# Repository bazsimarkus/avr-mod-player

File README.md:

# avr-mod-player

An ATmega32-based ProTracker MOD music player with AM29F040B parallel flash memory and stereo PWM audio output. Program a MOD file onto the flash chip, plug it in, and music starts playing.

---

## Table of Contents

- [Overview](#overview)
- [Features](#features)
- [Getting Started](#getting-started)
  - [What You Need](#what-you-need)
  - [Programming the Flash Chip](#programming-the-flash-chip)
  - [Building and Flashing the Firmware](#building-and-flashing-the-firmware)
- [Schematic](#schematic)
  - [Bill of Materials for the Main Board](#bill-of-materials-for-the-main-board)
- [How It Works](#how-it-works)
  - [Flash Memory Interface](#flash-memory-interface)
  - [Audio Output](#audio-output)
  - [MOD Playback Engine](#mod-playback-engine)
  - [Channel Activity LEDs](#channel-activity-leds)
  - [Power Supply and Protection](#power-supply-and-protection)
- [Speaker Extension Board](#speaker-extension-board)
  - [Bill of Materials for the Speaker Extension Board](#bill-of-materials-for-the-speaker-extension-board)
- [Documentation](#documentation)
- [Acknowledgments](#acknowledgments)

---

## Overview

This is a standalone hardware MOD file player built around the ATmega32A microcontroller. It reads ProTracker .MOD files directly from an AM29F040B parallel NOR flash chip and outputs stereo audio through RCA connectors using PWM and analog filtering. Four green LEDs flash in time with the music, one per channel, showing which voices are active.

The concept is simple: program a MOD file onto the flash chip, plug it into the socket, flip the power switch, and music starts playing immediately. No SD cards, no file systems, no menus. Just a chip full of music and a microcontroller that knows how to play it. If you want to listen to a different track, pull the flash chip out of its socket, erase it, program a new file, and put it back.

My main inspiration was [MadWizard's AVR MOD player](https://www.madwizard.org/electronics/projects/modplayer). That project also used the AM29F040 flash chip, which led me down this path. Since I had no way to program these chips, I ended up designing my own flash programmer, available as a separate project: [amd-flash-programmer](https://github.com/bazsimarkus/amd-flash-programmer).

---

## Features

- ATmega32A microcontroller running at 16 MHz external crystal
- AM29F040B 512KB parallel NOR flash for MOD file storage (socketed for easy swapping)
- Stereo audio output through dual RCA connectors
- MCP6022 dual rail-to-rail op-amp based analog output filtering
- 74HC595 shift register driving four green 3mm channel activity LEDs
- 4-channel ProTracker MOD format playback with effects (arpeggio, portamento, vibrato, volume slide, and more)
- 16 kHz PWM sample rate via Timer1, stereo hard-panned per ProTracker convention (channels 1 and 4 left, channels 2 and 3 right)
- 10-pin ISP header for in-circuit programming via USBasp
- 9-12V DC barrel jack power input with L7805 5V regulator
- 1N5819 Schottky diode protection preventing backfeed between DC jack and ISP programmer power
- ON/OFF toggle switch and reset button
- Pin header for the optional LM386 speaker extension board
- Designed in KiCad, full schematic and PCB files included

---

## Getting Started

### What You Need

- The assembled AVR MOD Player board
- A USBasp programmer (or any AVR ISP programmer)
- A way to program the AM29F040B flash chip (e.g. [amd-flash-programmer](https://github.com/bazsimarkus/amd-flash-programmer))
- A ProTracker .MOD file (max 512KB to fit on the flash chip)
- avr-gcc and avrdude installed on your system
- An RCA audio cable or the speaker extension board for output

### Programming the Flash Chip

1. Find a MOD file you want to play. [The Mod Archive](https://modarchive.org/) has a large collection of free tracks. Some personal favorites: Maktone - Vanishing Colors, LHS - It's a Good Day, Random Voice - Monday.

2. Remove the AM29F040B from its socket on the player board.

3. Program the raw .MOD file onto the flash chip starting at address 0x00000 using the [amd-flash-programmer](https://github.com/bazsimarkus/amd-flash-programmer) or any compatible flash programmer.

4. Place the programmed flash chip back into the socket on the player board.

5. Flip the power switch. The music starts playing immediately.

### Building and Flashing the Firmware

The firmware is a single C source file (`avr-mod-player/main.c`) targeting the ATmega32A at 16 MHz. It has no external dependencies beyond standard avr-libc. It links against libm for the math routines.

#### Method 1: Command line with avr-gcc and avrdude

Install avr-gcc and avrdude for your platform (on Debian/Ubuntu: `sudo apt install gcc-avr avr-libc avrdude`; on Windows, install WinAVR or the Microchip AVR toolchain).

Navigate to the `avr-mod-player` directory and run:

```sh
avr-gcc -mmcu=atmega32 -DF_CPU=16000000UL -O1 \
    -funsigned-char -funsigned-bitfields \
    -ffunction-sections -fdata-sections \
    -fpack-struct -fshort-enums \
    -Wall -o main.elf main.c -lm

avr-objcopy -O ihex main.elf main.hex
```

Then flash with your USBasp programmer:

```sh
avrdude -c usbasp -p m32 -U flash:w:main.hex
```

#### Method 2: MPLAB X IDE

The repository includes an MPLAB X IDE project in the `avr-mod-player/nbproject` directory. The project has two build configurations:

- **default**: Compiles only, produces the hex file.
- **flash**: Identical to default, but runs avrdude automatically after a successful build to flash the connected board via USBasp. The post-build step is:

```
avrdude -c usbasp -p m32 -U flash:w:${ImagePath}
```

With the flash configuration selected, clicking Build Main Project compiles the firmware and programs the board in a single step.

The project was developed with MPLAB X IDE v6.25 and the Microchip ATmega_DFP 3.3.279 device pack. The compiler is avr-gcc 5.4.0.

---

## Schematic

The full KiCad project files (schematic, PCB layout, and project file) are in the `schematic/` directory.

### Bill of Materials for the Main Board

| Ref | Value | Description | Qty |
|-----|-------|-------------|-----|
| **ICs** ||||
| U1 | ATmega32A-P | 16 MHz, 32 KB Flash, 2 KB SRAM, DIP-40 | 1 |
| U2 | AM29F040B-90PC | 4 Mbit NOR flash (512K×8), 90 ns, DIP-32 | 1 |
| U3 | 74HC595 | 8-bit shift register, 3-state outputs, DIP-16 | 1 |
| U4 | MCP6022 | Dual rail-to-rail op-amp, DIP-8 | 1 |
| U5 | L7805 | 5 V 1.5 A linear voltage regulator, TO-220 | 1 |
| **Crystal** ||||
| Y1 | 16 MHz | HC49-U vertical | 1 |
| **Capacitors (polarized)** ||||
| C1 | 10 µF | Electrolytic, radial, D4.0 mm P2.00 mm | 1 |
| C7 | 220 µF | Electrolytic, radial, D5.0 mm P2.00 mm | 1 |
| C8 | 220 µF | Electrolytic, radial, D5.0 mm P2.00 mm | 1 |
| C9 | 10 µF | Electrolytic, radial, D4.0 mm P2.00 mm | 1 |
| C12 | 10 µF | Electrolytic, radial, D4.0 mm P2.00 mm | 1 |
| **Capacitors (unpolarized)** ||||
| C2 | 100 nF | Film/MLCC, P5.00 mm | 1 |
| C3 | 22 pF | Ceramic, P2.50 mm | 1 |
| C4 | 22 pF | Ceramic, P2.50 mm | 1 |
| C5 | 10 nF | Ceramic disc, P2.50 mm | 1 |
| C6 | 10 nF | Ceramic disc, P2.50 mm | 1 |
| C10 | 0.33 µF | Film, P5.00 mm | 1 |
| C11 | 0.1 µF | Film, P5.00 mm | 1 |
| C13 | 100 nF | Film/MLCC, P5.00 mm | 1 |
| C14 | 100 nF | Film/MLCC, P5.00 mm | 1 |
| C15 | 100 nF | Film/MLCC, P5.00 mm | 1 |
| **Resistors (all 1/4 W axial)** ||||
| R1, R2 | 4.7 kΩ | PWM filter pull-up | 2 |
| R3, R4, R7, R8, R9, R10, R12 | 10 kΩ | Pull-ups / biasing / LED current limit | 7 |
| R5, R6 | 1 kΩ | Audio output series | 2 |
| R11 | 470 Ω | Power LED current limiter | 1 |
| **Diodes** ||||
| D1, D2, D3, D4 | LED 3 mm green | Channel activity indicators | 4 |
| D5 | 1N4001 | 50 V 1 A rectifier, DO-41 | 1 |
| D6 | LED 5 mm red | Power indicator | 1 |
| D7 | 1N5819 | 40 V 1 A Schottky, DO-41 (reverse polarity protection) | 1 |
| **Switches** ||||
| S1 | Toggle 7×7 mm DPDT | Power on/off (E-Switch TL2230OAF140) | 1 |
| S2 | Tact 6×6 mm | Reset (CUI TS02-66-100-BK-260-LCR-D) | 1 |
| **Connectors** ||||
| J1 | 2×5 shrouded box header | USBasp ISP header (Würth 61201021621) | 1 |
| J2 | DC-005 barrel jack | 2.1 mm center-positive | 1 |
| J3 | Dual RCA (AV2-8.4-45) | Stereo audio output | 1 |
| J4 | 2×4 pin socket | Speaker board expansion, 2.54 mm | 1 |
| **Recommended sockets** ||||
| - | 40-pin DIP socket | For U1 (ATmega32A) | 1 |
| - | 32-pin DIP socket | For U2 (AM29F040B) | 1 |
| - | 16-pin DIP socket | For U3 (74HC595) | 1 |
| - | 8-pin DIP socket | For U4 (MCP6022) | 1 |

---

## How It Works

### Flash Memory Interface

The AM29F040B is a 512KB parallel NOR flash chip in a 32-pin DIP package. The ATmega32A addresses it using nearly all of its available I/O pins:

- PORTA (PA0-PA7): Address lines A0-A7
- PORTB (PB0-PB7): Address lines A8-A15
- PORTD (PD0-PD2): Address lines A16-A18
- PORTC (PC0-PC7): Data bus DQ0-DQ7 (configured as input)

This gives 19 address lines, enough for the full 512KB address space. The chip enable (CE#) and output enable (OE#) pins are active (directly connected to ground), meaning the flash is always outputting data on the bus. The write enable (WE#) pin is pulled high permanently with a resistor, since the player board never writes to the flash. This simplified design was necessary because the ATmega32A does not have enough free pins to control WE# dynamically.

Reading a byte from flash is a single function call: set PORTA, PORTB, and the lower bits of PORTD to the desired address, wait two CPU cycles for the flash access time, then read PINC. At 16 MHz, this gives about 187 ns of access time, well within the 90 ns rating of the AM29F040B-90PC.

### Audio Output

Stereo audio is generated using Timer1 in 8-bit fast PWM mode. The two PWM outputs (OC1A on PD5 for left, OC1B on PD4 for right) run at a carrier frequency of 62.5 kHz (16 MHz / 256), which is well above the audible range.

The raw PWM signals pass through a low-pass filter built around the MCP6022 dual rail-to-rail op-amp. Each channel has its own filter section: a 10nF capacitor and a 4.7k resistor form the RC low-pass, and the op-amp buffers and drives the output through a 220uF coupling capacitor to the RCA connector. The coupling capacitor removes the DC offset so only the audio AC signal reaches the amplifier or speakers.

### MOD Playback Engine

The firmware implements a ProTracker-compatible 4-channel MOD player. Timer0 fires an interrupt at exactly 16,000 Hz, which pulls samples from a ring buffer and writes them to the PWM registers. The main loop continuously fills that buffer by mixing the four channels.

The MOD file format stores music as a sequence of patterns. Each pattern has 64 rows, and each row has four cells (one per channel). Each cell can trigger a sample at a given pitch, change the volume, or apply an effect. At startup, the firmware parses the MOD header from flash to locate the sample data and pattern data, then begins sequencing through the song.

The engine supports the following ProTracker effects:

- 0xy: Arpeggio
- 1xx: Portamento up
- 2xx: Portamento down
- 3xx: Tone portamento
- 4xy: Vibrato
- 9xx: Sample offset
- Axy: Volume slide
- Bxx: Pattern jump
- Cxx: Set volume
- Dxx: Pattern break
- Fxx: Set speed/tempo
- E1y/E2y: Fine portamento
- E9y: Retrigger note
- EAy/EBy: Fine volume slide
- ECy: Note cut

Pitch is calculated using 16.16 fixed-point arithmetic. The playback step for each channel is derived from the Amiga PAL clock constant (3,546,895 Hz) divided by the channel's current period value, scaled to the 16 kHz output rate. This gives sample-accurate pitch reproduction matching the original Amiga hardware.

The MOD file format specification used to build this player is included in the repository at `docs/mod-spec.txt` (sourced from [eblong.com/zarf/blorb/mod-spec.txt](https://www.eblong.com/zarf/blorb/mod-spec.txt)).

### Channel Activity LEDs

Four green 3mm LEDs (D1-D4) are driven by a 74HC595 shift register connected to three pins on PORTD. Each time a note triggers on a channel, the corresponding LED lights up for approximately 60 milliseconds (3 sequencer ticks). This creates a short flash locked to the beat, giving a visual indication of which channels are active. The LEDs are updated once per sequencer tick in the main audio loop.

### Power Supply and Protection

The board is powered from a 9-12V DC barrel jack. An L7805 voltage regulator provides the 5V rail for all digital and analog circuitry. A 1N4001 rectifier diode on the DC input provides reverse polarity protection.

A 1N5819 Schottky diode sits between the ISP header's VCC pin and the board's 5V rail. When the board is powered from the DC jack, the Schottky diode prevents the regulated 5V from backfeeding into the programmer. When the board is powered from the programmer (for firmware development without the DC supply connected), the Schottky diode conducts and powers the board from the programmer's VCC. This protects both the L7805 regulator and the programmer from conflicting voltage sources.

---

## Speaker Extension Board

An optional LM386 speaker extension board can be connected to the 2x4 pin header (J4) on the main board. It mixes the left and right channels through two 300k resistors into a volume trimmer, feeds the signal through an LM386 audio power amplifier, and drives a small 23mm 8-ohm speaker. The board connects directly to the pin header and receives both audio signals and power from the main board.

The KiCad project files for the speaker board are in `extension-boards/speaker-board/`.

### Bill of Materials for the Speaker Extension Board

| Ref | Value | Description | Qty |
|-----|-------|-------------|-----|
| **ICs** ||||
| U1 | LM386 | Low-voltage audio power amplifier, DIP-8 | 1 |
| **Capacitors (polarized)** ||||
| C1 | 100 µF | Electrolytic, radial, D5.0 mm P2.00 mm | 1 |
| C3 | 1 µF | Electrolytic, radial, D4.0 mm P2.00 mm | 1 |
| C4 | 10 µF | Electrolytic, radial, D4.0 mm P2.00 mm (bypass) | 1 |
| C6 | 220 µF | Electrolytic, radial, D5.0 mm P2.00 mm (output coupling) | 1 |
| **Capacitors (unpolarized)** ||||
| C2 | 0.1 µF | Film, P5.00 mm (decoupling) | 1 |
| C5 | 47 nF | Ceramic disc, P2.50 mm (Zobel network) | 1 |
| **Resistors (all 1/4 W axial)** ||||
| R1, R2 | 300 kΩ | Input mixing (L + R → mono) | 2 |
| R3 | 10 Ω | Zobel network series | 1 |
| **Potentiometer** ||||
| RV1 | Trimpot 3362-P | Volume adjustment | 1 |
| **Speaker** ||||
| LS1 | CVS-2308 | 23 mm, 0.1 W, 8 Ω (CUI Devices) | 1 |
| **Connectors** ||||
| J1 | 2×4 pin header | Mates with main board J4, 2.54 mm vertical | 1 |
| **Recommended sockets** ||||
| - | 8-pin DIP socket | For U1 (LM386) | 1 |

---

## Documentation

The `docs/` directory contains:

- `mod-spec.txt`: The ProTracker MOD file format specification used as reference for the playback engine (from [eblong.com](https://www.eblong.com/zarf/blorb/mod-spec.txt))

---

## Acknowledgments

- [MadWizard](https://www.madwizard.org/electronics/projects/modplayer) for the original AVR MOD player project that inspired this build
- [The Mod Archive](https://modarchive.org/) for the collection of freely available MOD files
- The ProTracker MOD format specification from [eblong.com](https://www.eblong.com/zarf/blorb/mod-spec.txt)

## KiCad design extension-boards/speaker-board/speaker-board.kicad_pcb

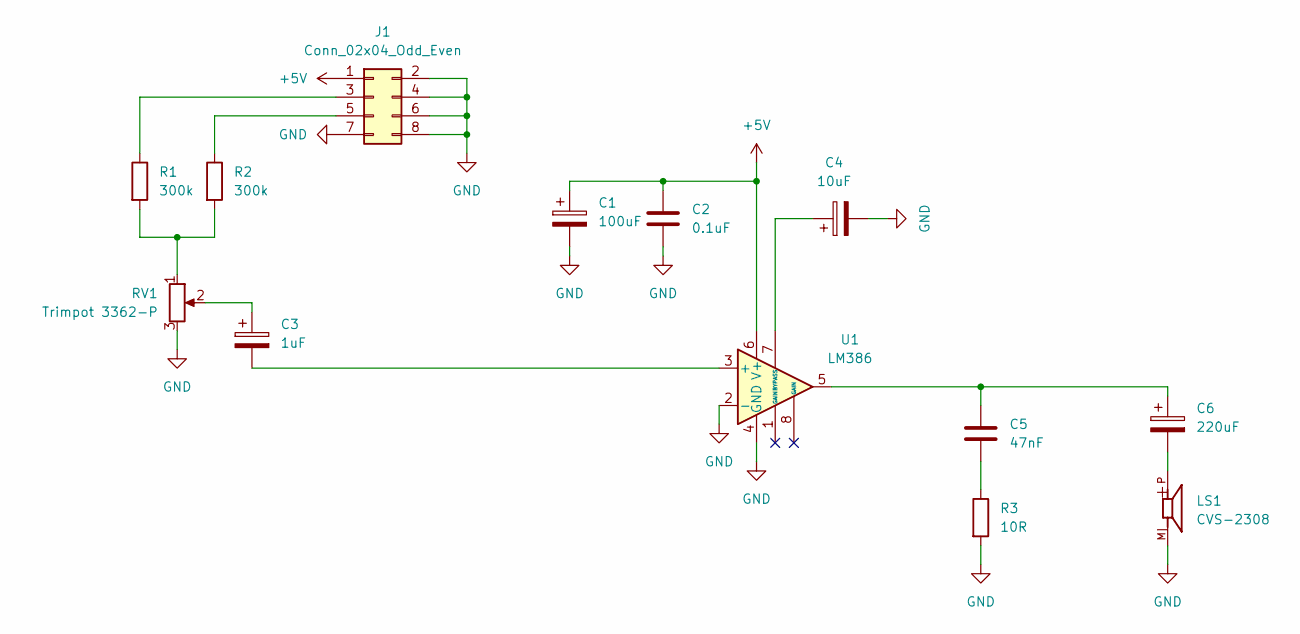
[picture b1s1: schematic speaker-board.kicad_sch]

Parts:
C1: 100uF; CP_Radial_D5.0mm_P2.00mm
C2: 0.1uF; C_100nF_L7.0mm_W2.5mm_P5.00mm
C3: 1uF; CP_Radial_D4.0mm_P2.00mm
C4: 10uF; CP_Radial_D4.0mm_P2.00mm
C5: 47nF; C_Disc_D3.0mm_W1.6mm_P2.50mm
C6: 220uF; CP_Radial_D5.0mm_P2.00mm
J1: Conn_02x04_Odd_Even; PinHeader_2x04_P2.54mm_Vertical
LS1: CVS-2308; SPKR_CVS-2308
R1, R2: 300k; R_10k_Axial_DIN0207
R3: 10R; R_10k_Axial_DIN0207
RV1: Trimpot 3362-P; Trimpot 3386F
U1: LM386; DIP-8_W7.62mm

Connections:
+5V: C1.1, C2.2, J1.1, U1.6 (V+)
GND: C1.2, C2.1, C4.2, J1.2, J1.4, J1.6, J1.7, J1.8, LS1.M, R3.2, RV1.3, U1.2 (-), U1.4 (GND)
unnamed: C3.1, RV1.2
unnamed: C5.1, R3.1
unnamed: C5.2, C6.1, U1.5
unnamed: C6.2, LS1.P
unnamed: J1.3, R1.1
unnamed: J1.5, R2.1
unnamed: R1.2, R2.2, RV1.1
unnamed: C3.2, U1.3 (+)
unnamed: C4.1, U1.7 (BYPASS)

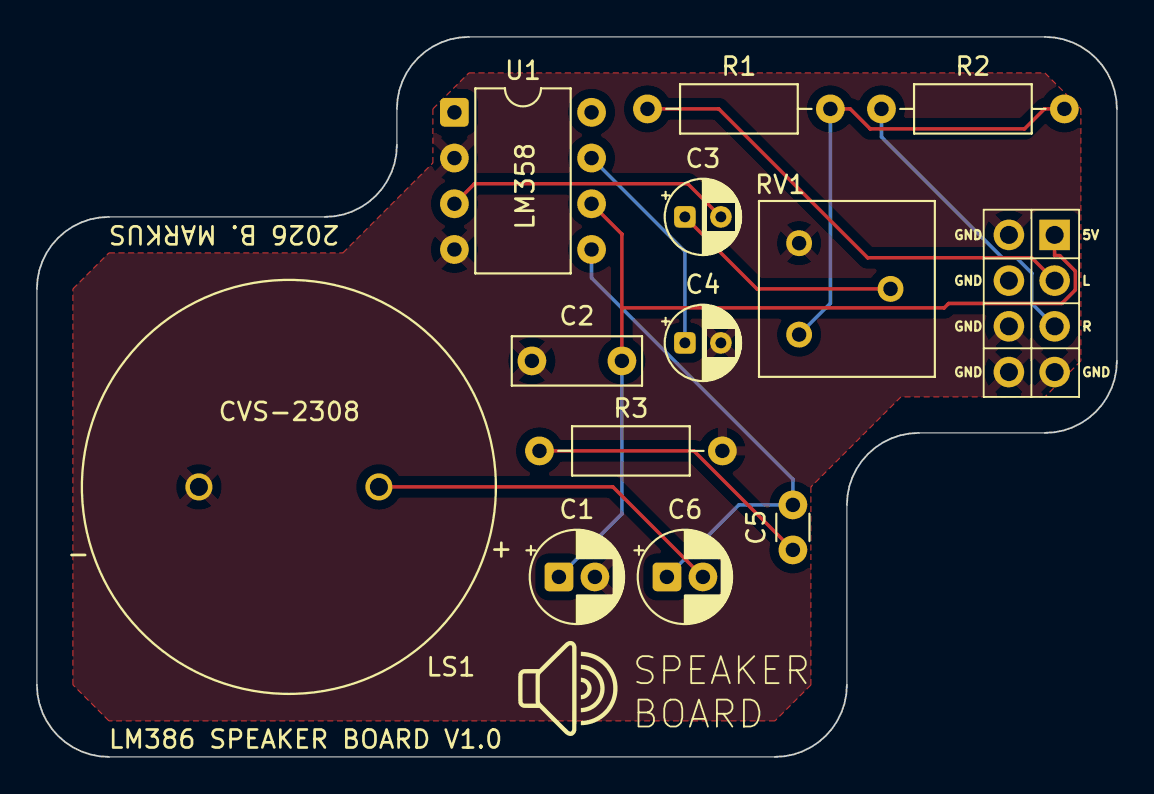
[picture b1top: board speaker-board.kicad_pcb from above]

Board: 2 copper layers, 60.0 x 40.0 mm, 14 parts (1 on the bottom side), 11 nets.

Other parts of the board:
G1: LOGO

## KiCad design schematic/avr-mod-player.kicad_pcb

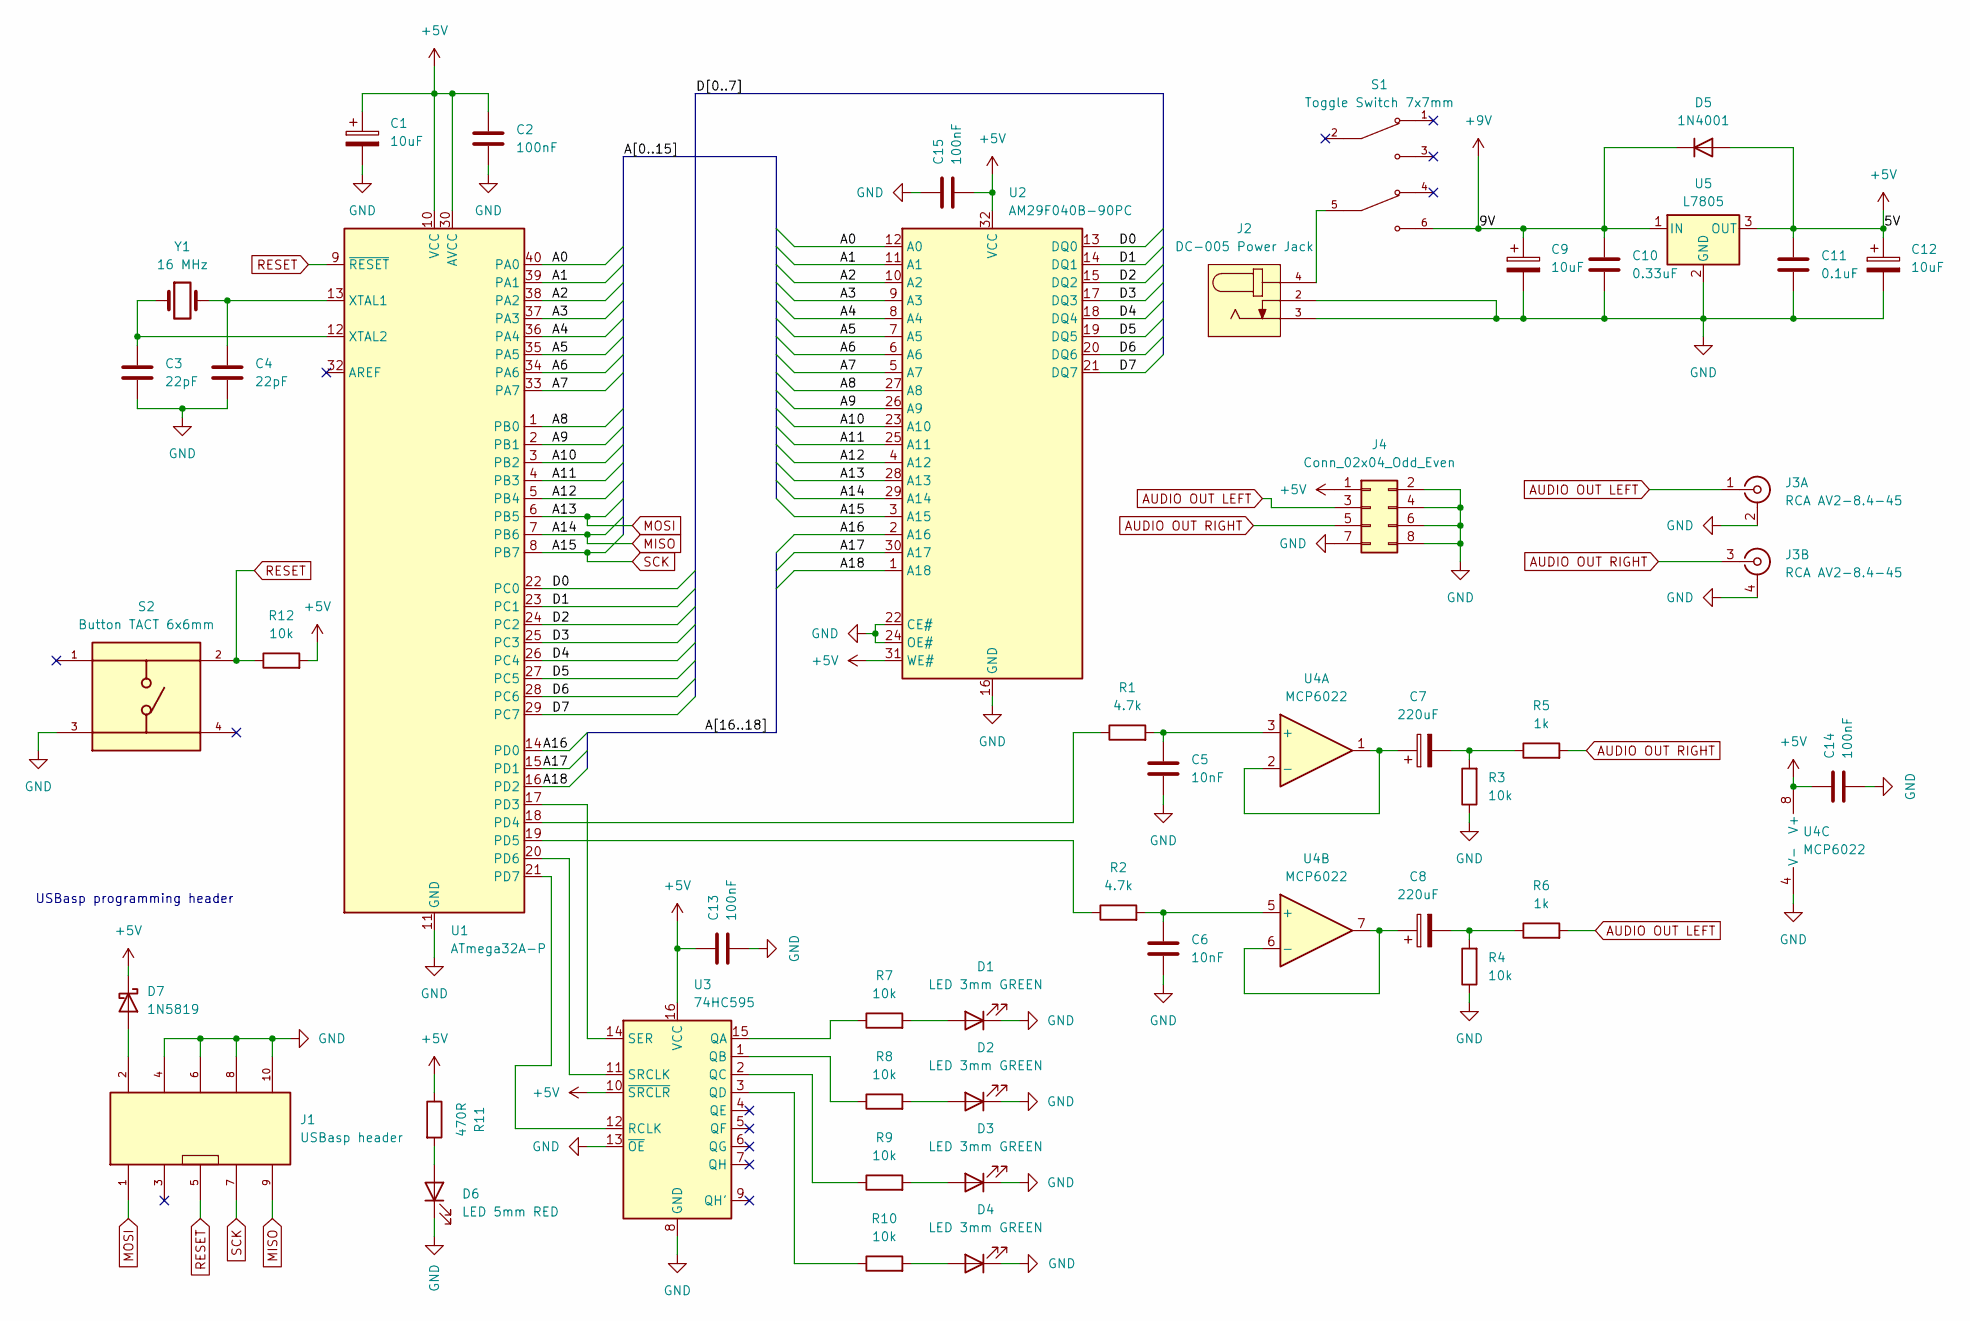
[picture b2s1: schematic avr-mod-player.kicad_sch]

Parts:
C1, C9, C12: 10uF; CP_Radial_D4.0mm_P2.00mm
C2, C13, C14, C15: 100nF; C_100nF_L7.0mm_W2.5mm_P5.00mm
C3, C4: 22pF; C_Rect_L4.6mm_W2.0mm_P2.50mm_MKS02_FKP02
C5, C6: 10nF; C_Disc_D3.0mm_W1.6mm_P2.50mm
C7, C8: 220uF; CP_Radial_D5.0mm_P2.00mm
C10: 0.33uF; C_100nF_L7.0mm_W2.5mm_P5.00mm
C11: 0.1uF; C_100nF_L7.0mm_W2.5mm_P5.00mm
D1, D2, D3, D4: LED 3mm GREEN; LED_D3.0mm_GREEN
D5: 1N4001; D_DO-41_SOD81_P10.16mm_Horizontal
D6: LED 5mm RED; LED_D5.0mm_RED
D7: 1N5819; D_DO-41_SOD81_P10.16mm_Horizontal
J1: USBasp header; 2x5 Shrouded Box Header
J2: DC-005 Power Jack
J3: RCA AV2-8.4-45; AV2-8.4-45
J4: Conn_02x04_Odd_Even; PinSocket_2x04_P2.54mm_Vertical
R1, R2: 4.7k; R_470_Axial_DIN0207
R3, R4, R12: 10k; R_10k_Axial_DIN0207
R5, R6: 1k; R_1k_Axial_DIN0207
R7, R8, R9, R10: 10k; R_470_Axial_DIN0207
R11: 470R; R_470_Axial_DIN0207
S1: Toggle Switch 7x7mm; PARTREV E; DigiKey_Part_Number EG6032-ND
S2: Button TACT 6x6mm; PARTREV 1.0
U1: ATmega32A-P; DIP-40_W15.24mm
U2: AM29F040B-90PC; DIP-32_W15.24mm
U3: 74HC595; DIP-16_W7.62mm
U4: MCP6022; DIP-8_W7.62mm
U5: L7805; TO-220-3_Vertical
Y1: 16 MHz; Crystal_HC49-U_Vertical

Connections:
+5V: C1.1, C2.1, C11.2, C12.1, C13.1, C14.1, C15.2, D5.2 (A), D7.1 (K), J4.1, R11.1, R12.2, U1.10 (VCC), U1.30 (AVCC), U2.31 (WE#), U2.32 (VCC), U3.10 (~SRCLR), U3.16 (VCC), U4.8 (V+), U5.3 (OUT)
+9V: C9.1, C10.2, D5.1 (K), S1.6, U5.1 (IN)
/A0: U1.40 (PA0), U2.12 (A0)
/A1: U1.39 (PA1), U2.11 (A1)
/A2: U1.38 (PA2), U2.10 (A2)
/A3: U1.37 (PA3), U2.9 (A3)
/A4: U1.36 (PA4), U2.8 (A4)
/A5: U1.35 (PA5), U2.7 (A5)
/A6: U1.34 (PA6), U2.6 (A6)
/A7: U1.33 (PA7), U2.5 (A7)
/A8: U1.1 (PB0), U2.27 (A8)
/A9: U1.2 (PB1), U2.26 (A9)
/A10: U1.3 (PB2), U2.23 (A10)
/A11: U1.4 (PB3), U2.25 (A11)
/A12: U1.5 (PB4), U2.4 (A12)
/A16: U1.14 (PD0), U2.2 (A16)
/A17: U1.15 (PD1), U2.30 (A17)
/A18: U1.16 (PD2), U2.1 (A18)
/D0: U1.22 (PC0), U2.13 (DQ0)
/D1: U1.23 (PC1), U2.14 (DQ1)
/D2: U1.24 (PC2), U2.15 (DQ2)
/D3: U1.25 (PC3), U2.17 (DQ3)
/D4: U1.26 (PC4), U2.18 (DQ4)
/D5: U1.27 (PC5), U2.19 (DQ5)
/D6: U1.28 (PC6), U2.20 (DQ6)
/D7: U1.29 (PC7), U2.21 (DQ7)
AUDIO OUT LEFT: J3.1 (In1), J4.3, R6.2
AUDIO OUT RIGHT: J3.3 (In2), J4.5, R5.2
GND: C1.2, C2.2, C3.2, C4.2, C5.2, C6.2, C9.2, C10.1, C11.1, C12.2, C13.2, C14.2, C15.1, D1.1 (K), D2.1 (K), D3.1 (K), D4.1 (K), D6.1 (K), J1.4, J1.6, J1.8, J1.10, J2.2, J2.3, J3.2 (Ext1), J3.4 (Ext2), J4.2, J4.4, J4.6, J4.7, J4.8, R3.1, R4.1, S2.3, U1.11 (GND), U1.31 (GND), U2.16 (GND), U2.22 (CE#), U2.24 (OE#), U3.8 (GND), U3.13 (~OE), U4.4 (V-), U5.2 (GND)
MISO: J1.9, U1.7 (PB6), U2.29 (A14)
MOSI: J1.1, U1.6 (PB5), U2.28 (A13)
unnamed: C7.2, R3.2, R5.1
unnamed: C8.2, R4.2, R6.1
unnamed: D1.2 (A), R7.2
unnamed: D2.2 (A), R8.2
unnamed: D3.2 (A), R9.2
unnamed: D4.2 (A), R10.2
unnamed: D6.2 (A), R11.2
unnamed: D7.2 (A), J1.2
unnamed: J2.4, S1.5
unnamed: U1.17 (PD3), U3.14 (SER)
unnamed: R1.1, U1.18 (PD4)
unnamed: R2.1, U1.19 (PD5)
unnamed: U1.20 (PD6), U3.11 (SRCLK)
unnamed: U1.21 (PD7), U3.12 (RCLK)
unnamed: C4.1, U1.13 (XTAL1), Y1.2
unnamed: C3.1, U1.12 (XTAL2), Y1.1
unnamed: R7.1, U3.15 (QA)
unnamed: R8.1, U3.1 (QB)
unnamed: R9.1, U3.2 (QC)
unnamed: R10.1, U3.3 (QD)
unnamed: C5.1, R1.2, U4.3 (+)
unnamed: C7.1, U4.1, U4.2 (-)
unnamed: C6.1, R2.2, U4.5 (+)
unnamed: C8.1, U4.6 (-), U4.7
RESET: J1.5, R12.1, S2.2, U1.9 (~RESET)
SCK: J1.7, U1.8 (PB7), U2.3 (A15)

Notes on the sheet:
USBasp programming header

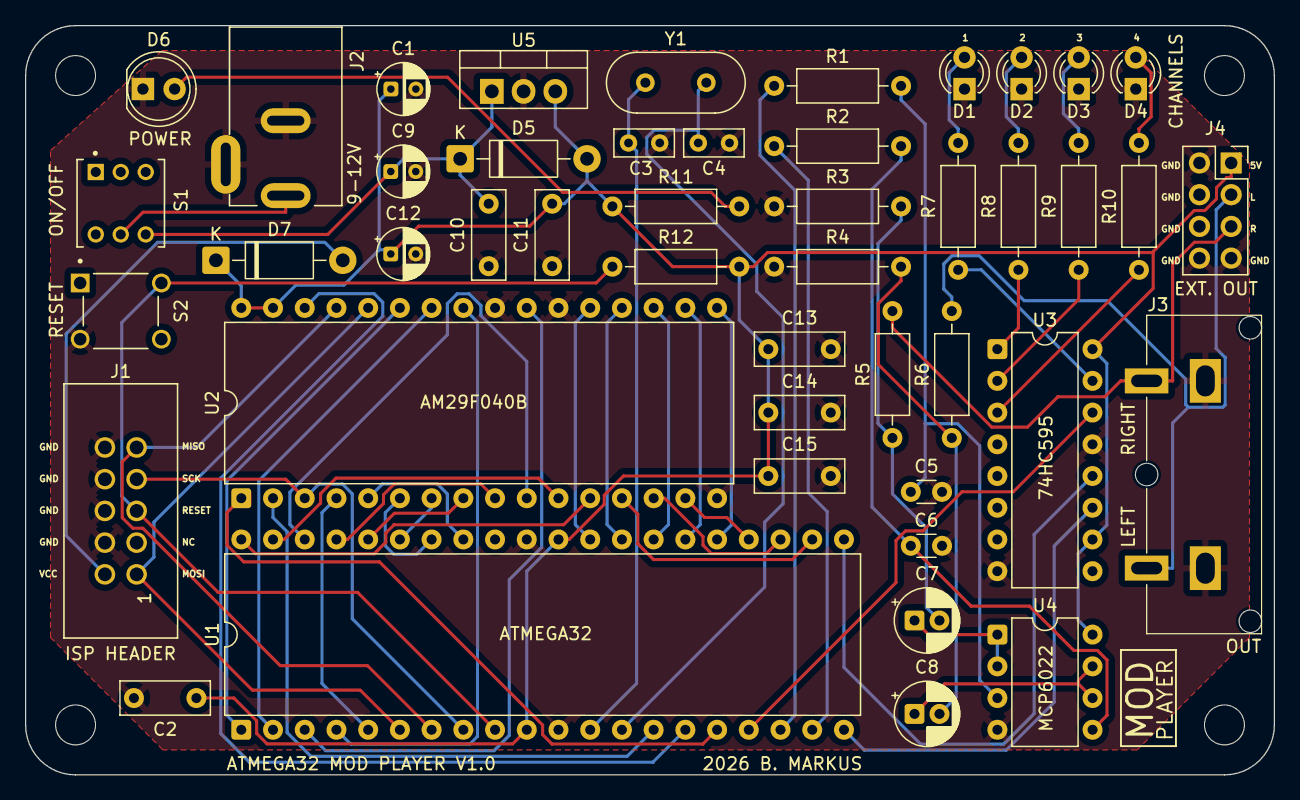
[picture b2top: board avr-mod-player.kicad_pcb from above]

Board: 2 copper layers, 100.0 x 60.0 mm, 50 parts (0 on the bottom side), 57 nets.

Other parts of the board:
MH1, MH2, MH3, MH4: MountingHole_3.2mm_M3_DIN965

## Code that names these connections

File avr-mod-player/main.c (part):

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 *
 * Hardware:
 *   - AM29F040B parallel NOR flash (512KB) hard-wired to PORTA (A0-A7),
 *     PORTB (A8-A15), and PD0..PD2 (A16-A18). PORTC = data bus (input).
 *   - Stereo PWM audio output via Timer1: OC1A (PD5) = Left, OC1B (PD4) = Right.
 *   - 74HC595 shift register for 4-channel LED visualisation via PD3/PD6/PD7.
 *   - Timer0 fires the audio ISR at exactly 16,000 Hz.
 *
 * Converted from Arduino sketch to bare-metal avr-gcc / MPLAB X.
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#define BUF_SIZE         128   // Must be a power of two (ring-buffer)

// Shift Register Pins (all on PORTD)
#define SER_PIN    PD3   // Serial data in
#define SRCLK_PIN  PD6   // Shift register clock
#define RCLK_PIN   PD7   // Latch / storage clock

// =========================================================================
// PROGMEM TABLES
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// =========================================================================

// Reads a single byte from the hardwired AM29F040B flash at 'addr'.
// PORTA = A0-A7, PORTB = A8-A15, PD0-PD2 = A16-A18, PORTC = data (input).
// The two NOPs after writing PORTD give the flash its required address
// setup + access time (max 150 ns; 2 cycles @ 16 MHz ? 125 ns + PORTD write ? 187.5 ns total).
inline uint8_t read_flash(uint32_t addr) {
    PORTA = addr & 0xFF;
    PORTB = (addr >> 8) & 0xFF;
    // Preserve PWM (PD4/PD5) and 74HC595 (PD3/PD6/PD7) pins; only touch PD0-PD2
    PORTD = (PORTD & 0xF8) | ((addr >> 16) & 0x07);

    // Wait for address propagation & flash access time (up to 150ns)
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
void hardware_init() {
    // --- I/O Direction ---
    DDRA  = 0xFF;   // PA0-PA7 ? Flash address bus A0-A7 (output)
    DDRB  = 0xFF;   // PB0-PB7 ? Flash address bus A8-A15 (output)
    DDRC  = 0x00;   // PC0-PC7 ? Flash data bus DQ0-DQ7 (input)
    PORTC = 0x00;   // Disable pull-ups on data bus inputs
    // PD0-PD2: A16-A18 (output), PD3: SER (output), PD4: OC1B/Right (output),
    // PD5: OC1A/Left (output), PD6: SRCLK (output), PD7: RCLK (output)
    DDRD  = 0xFF;

    // --- Audio PWM: Timer1 in 8-bit Fast PWM mode ---
    // OC1A (PD5) = Left channel, OC1B (PD4) = Right channel.
    // Non-inverted (clear on compare match, set at BOTTOM).
    // Carrier frequency = 16 MHz / 256 = 62.5 kHz (well above audible range).
    TCCR1A = (1 << COM1A1) | (1 << COM1B1) | (1 << WGM10); // 8-bit Fast PWM, non-inverted
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
ISR(TIMER0_COMP_vect) {
    if (rd_ptr != wr_ptr) {
        OCR1A = audio_buf_L[rd_ptr]; // Left  channel ? OC1A / PD5
        OCR1B = audio_buf_R[rd_ptr]; // Right channel ? OC1B / PD4
        rd_ptr = (rd_ptr + 1) & (BUF_SIZE - 1);
    }
}
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
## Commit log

2026-02-21 Add base code for ATmega32, add MPLAB X IDE project files, add .gitignore and clean repo
2026-02-22 Schematic updated
2026-02-22 MPLAB X IDE nbproject private folder deleted
2026-02-22 gitignore moved to project source folder
2026-03-02 Schematic migrated to KiCad 9
2026-03-04 PCB added to schematic folder
2026-03-05 Speaker extension board schematic and PCB added
2026-03-05 Schottky diode added to ISP header for protection
2026-03-05 Schematic: Silkscreen updated on boards
2026-03-07 Footprints updated, MPLAB X IDE build configurations updated
2026-05-09 Images and documentation added
